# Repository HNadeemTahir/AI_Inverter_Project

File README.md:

# Solar Inverter & MPPT Booster — Simulation to Hardware

NgSpice simulation and KiCad PCB design of a complete off-grid solar power system. The simulation uses manufacturer SPICE models (not ideal switches) and translates dsPIC30F2010 firmware logic into behavioral equations so the control loops can be validated before building hardware.

Two power conversion stages, developed across 10 versions:

1. **H-Bridge Inverter** — Single-phase 220V/50Hz pure sine wave output using FGY75T120SWD IGBTs, unipolar SPWM, closed-loop PI voltage regulation, electro-thermal monitoring, and hardware fault protection.
2. **4kW MPPT Boost Converter** — DC-DC front-end regulating a variable 120V–350V PV string to a stable 380V DC bus, controlled by a UC3843 analog controller slaved to a dsPIC30F2010 MCU.

---

## Note on Methodology

The workflow here — simulate with real device models, sweep parameters with Python, train a surrogate model, then route the PCB — is not specific to boost converters. The same approach works for any power stage where you need to predict switching losses and thermal behavior before committing to hardware. I have used variations of this on inverter gate drives, motor current loops, and industrial servo tuning.

---

## Project Phases at a Glance

| Version  | Focus Area               | Key Achievement                                      |
|:--------:|:-------------------------|:-----------------------------------------------------|
| V1.0     | Environment Setup        | NgSpice + library structure established              |
| V2.0     | Half-Bridge SPWM         | Ideal switching, basic sine generation               |
| V3.0     | Physical IGBT Models     | Real FGY75T120SWD switching behavior                 |
| V4.0     | Full H-Bridge + LC       | Unipolar SPWM, motor load, phase lag verified        |
| V5.0     | Closed-Loop PI Control   | ZMPT101B sensor delay, voltage regulation            |
| V6.1     | Dead-Time + Thermal      | 2µs shoot-through protection, Foster RC model        |
| V6.3     | Python Automation        | Batch simulation, CSV data extraction                |
| V6.5     | Modulation Benchmark     | THI + Dead-Time compensation matrix                  |
| V7.0     | Surrogate Model          | Scikit-Learn Random Forest predictor                 |
| V8.0     | 4kW MPPT Converter       | Feed-forward + PI boost, 3 test profiles             |
| V9.0     | UC3843 Control Loop      | Analog-digital MPPT integration, gate physics        |
| **V10.0**| **Hardware PCB**         | **KiCad layout, DRC-clean, 3D-verified**             |

---

## Hardware Implementation (KiCad)

The 4kW MPPT booster control board, designed in KiCad 9.0. DRC-clean. The schematic and layout match the UC3843 + dsPIC control architecture from V8.0 and V9.0 simulations.

### PCB 3D Render — Component Side

### PCB 3D Render — Isometric View

### Hardware Design Files

| File | Description |
|:-----|:------------|
| [`MPPT_Booster_4kW_Hardware.kicad_pro`](hardware/kicad/MPPT_Booster_4kW_Hardware.kicad_pro) | KiCad 9.0 project file |
| [`MPPT_Booster_4kW_Hardware.kicad_sch`](hardware/kicad/MPPT_Booster_4kW_Hardware.kicad_sch) | Full schematic (UC3843 + dsPIC + gate drivers + current sensing) |
| [`MPPT_Booster_4kW_Hardware.kicad_pcb`](hardware/kicad/MPPT_Booster_4kW_Hardware.kicad_pcb) | PCB layout with copper pours, clearance rules, and thermal relief |
| [`DRC.rpt`](hardware/kicad/DRC.rpt) | Design Rule Check report |

### Key Layout Decisions

- **High-current paths** (inductor → IGBT → diode → output caps) use wide copper pours with thermal relief pads to handle 20A+ continuous current
- **Gate driver isolation** — FOD3150 optoisolators provide galvanic separation between the dsPIC logic ground and the power stage ground
- **Current sensing** — INA181A2 shunt amplifier placed directly adjacent to the sense resistor to minimize noise pickup
- **Analog control section** — UC3843, slope compensation network, and RC timing components grouped together with short trace runs

---

## Version 9.0 — UC3843 Analog Control Loop Integration

This version implements the hardware-level control architecture of the 4kW MPPT booster. It moves beyond behavioral SPICE switches into a real analog control loop where a **UC3843 peak-current-mode PWM controller** is directly slaved to the **dsPIC30F2010** MCU via a KCL-balanced voltage summing node.

### Engineering Targets Achieved

| Target                                 | Method                                                | Status     |
|:---------------------------------------|:------------------------------------------------------|:----------:|
| Analog-digital MPPT interface          | KCL summing node on UC3843 Pin 2                      | ✅ Proven  |
| Cold-boot explosion prevention         | 10kΩ pull-up on dsPIC OC1 PWM line                    | ✅ Proven  |
| Precharge relay MCU isolation          | 2N2222 NPN driving 40A contactor coil                 | ✅ Proven  |
| Sub-harmonic oscillation fix           | 2N3904 NPN emitter-follower slope compensation        | ✅ Proven  |
| 100ns turn-on noise rejection          | 1kΩ + 470pF LEB filter on UC3843 Pin 3                | ✅ Proven  |
| IGBT Miller plateau characterization   | Asymmetric gate drive: 15Ω ON / 5.6Ω+D OFF            | ✅ Proven  |
| dsPIC PWM-to-analog conversion         | 10kΩ + 4.7µF RC filter: 3.3Hz cutoff                  | ✅ Proven  |

### Test 1 — MPPT Summing Node: dsPIC Duty Cycle Sweep

Four-point parametric sweep of the dsPIC OC1 PWM duty cycle. Proves the KCL summing node physics: at 25% duty cycle, Pin 2 settles below 2.50V and the UC3843 boosts at maximum power. At 50%–100%, Pin 2 rises above the 2.50V threshold and the converter shuts down in a controlled manner. The 10kΩ pull-up resistor ensures this safe state is the default during MCU boot.

| dsPIC PWM | RC Filter Output | Pin 2 Voltage | UC3843 State         |
|:---------:|:----------------:|:-------------:|:---------------------|
| 25%       | 1.25V            | 2.33V         | Boosting (MAX POWER) |
| 50%       | 2.50V            | 2.51V         | Shut Down            |
| 75%       | 3.75V            | 2.69V         | Shut Down            |
| 100%      | 5.00V            | 2.88V         | Shut Down            |

### Test 2 — Gate Capacitance Charge/Discharge Analysis

500µs high-resolution transient analysis of the asymmetric gate drive network on the STGW60H65DFB parallel IGBT pair. Characterizes the Miller Plateau crossing, threshold voltage events, and the turn-on/turn-off time constants resulting from the 15Ω / 5.6Ω+1N4148 resistor-diode network.

| Parameter            | Turn-ON                              | Turn-OFF                                            |
|:---------------------|:------------------------------------:|:---------------------------------------------------:|
| Gate Resistor        | 15 Ω                                 | 5.6 Ω + 1N4148                                      |
| Time Constant (τ)    | ~300 ns                              | ~112 ns                                             |
| Purpose              | di/dt limiting, diode recovery ctrl  | Miller effect suppression, shoot-through prevention |
| IGBT Threshold (Vth) | 6.0 V                                | 6.0 V                                               |
| Miller Plateau       | ~9 V                                 | ~9 V                                                |
| Full Saturation      | 15 V                                 | —                                                   |

### Test 3 — UC3843 Closed-Loop Boost Converter

Full closed-loop simulation of the UC3843 controlling the power stage. Shows the DC bus regulation, inductor current waveform, and the 20kHz gate drive signal across the full 60ms transient window.

### Test 4 — LEB Filter: 470ns Current Sense Propagation Delay

Step-response analysis of the Leading Edge Blanking (LEB) filter at UC3843 Pin 3. A simulated dead-short event causes the INA181 output to jump instantaneously to 1.5V. The 1kΩ + 470pF RC filter delays the signal reaching the 1.0V trip threshold by 470ns — exactly the blanking window required to mask IGBT turn-on current spikes while remaining fast enough to detect a genuine short circuit within one switching cycle.

---

## Version 8.0 — 4kW MPPT Boost Converter

Full power-stage simulation of the 4kW DC-DC booster. Feed-forward + PI control architecture handles 3-panel to 8-panel PV string inputs.

### Booster Specifications

| Parameter           | Value                                |
|:--------------------|:-------------------------------------|
| Input Range         | 120V – 350V DC                       |
| Output              | 380V DC (regulated)                  |
| Max Power           | 4000W                                |
| Switching Frequency | 20kHz                                |
| IGBTs               | 2× STGW60H65DFB (650V/60A, parallel) |
| Boost Diode         | STTH3006D (600V/30A, 35ns Trr)       |
| Gate Driver         | FOD3150 (optically isolated)         |
| Control             | Feed-Forward + PI with anti-windup   |

### Validated Test Profiles

| Profile        | Input | Load  | Steady State | Verdict  |
|:---------------|:-----:|:-----:|:------------:|:--------:|
| 3-Panel String | 120V  | 1500W | 380V flat    | **PASS** |
| 5-Panel String | 250V  | 3000W | 380V flat    | **PASS** |
| 8-Panel String | 350V  | 4000W | 380V ±10V†   | **PASS** |

† Bounded oscillation at 350V is LC resonance at near-unity boost ratio. Eliminated in firmware by a single-coefficient EMA filter: `vbus_filt = 0.015 * raw + 0.985 * filt`.

### Profile 1: 120V → 380V (1500W, Boost Ratio 3.17×)

### Profile 2: 250V → 380V (3000W, Boost Ratio 1.52×)

### Profile 3: 350V → 380V (4000W, Boost Ratio 1.09×)

### Critical Design Findings
- **Feed-forward is mandatory** at high boost ratios. Without it, the PI controller cannot reach 68% duty cycle fast enough, producing 250A+ inductor current spikes on startup.
- **Load connection sequence matters** — connecting the inverter load before the DC bus reaches 90% of target produces 400A+ surge currents due to the discharged output capacitor acting as a short circuit.
- **Firmware EMA filter required** at 350V operating point to damp the LC resonance visible in the 350V simulation profile.

---

## Version 7.0 — Surrogate Model (Scikit-Learn)

A Random Forest Regression model trained on 204 NgSpice simulations generated by the parametric data factory. The predictor approximates IGBT junction temperature, efficiency, and AC output voltage for any input condition in under 0.01 seconds — eliminating the need to run a full transient simulation during firmware tuning.

### Surrogate Model Accuracy

### Instant Performance Predictor

---

## Version 6.5 — Modulation Strategy Benchmark

Four independently toggled modulation strategies benchmarked against each other using a parametric sweep across 400V DC link conditions.

### Strategy Matrix

| THI | DT Comp | Strategy        | V_rms      | Tj_max     | Efficiency |
|:---:|:-------:|:----------------|:----------:|:----------:|:----------:|
| OFF | OFF     | Bare SPWM       | 188.7V     | 45.9°C     | 97.2%      |
| OFF | ON      | SPWM + DT Comp  | 192.1V     | 45.5°C     | 98.1%      |
| ON  | OFF     | THI Flat-Top    | 192.8V     | 45.9°C     | 97.2%      |
| ON  | ON      | THI + DT Comp   | **195.5V** | **45.5°C** | 97.9%      |

The combined strategy recovers 6.8V of AC output. Uncompensated dead-time introduces harmonic distortion that recirculates as I²R heat — compensating it in firmware improves both output voltage and thermal efficiency simultaneously.

---

## Inverter Simulation Results (V6.5 Reference)

### Output Voltage — Inductive Motor Load

*50Hz output into 20Ω/100mH R-L load. Peak ±311V.*

### Voltage-Current Phase Lag

*Current lags voltage by ~57°. Confirmed: arctan(2π × 50 × 0.1 / 20) = 57.5°.*

### PI Controller: Reference vs Feedback

*ZMPT101B-delayed feedback vs reference. PI controller achieves tracking within 2 cycles.*

### PI Controller Internal Signals

*Error and integral signals. Integral term stabilizes by 20ms.*

### ZMPT101B Sensor Delay

*200µs RC group delay (2kΩ / 100nF) modeled from physical transformer + PCB filter.*

### Dead-Time Protection — Gate Signals

*~2µs dead-time gap between Leg A HS and LS transitions, matching dsPIC DTCON1 register.*

### DC Bus Energy Flow

*Negative current = energy delivery to load. Positive spikes at zero-crossings = inductive freewheeling through body diodes.*

### Short-Circuit Protection (50A Trip)

*0.1Ω dead-short at t=25ms. CT + comparator trips INT0 latch at 50A primary. Current decays through freewheeling path within 1ms.*

### Electro-Thermal IGBT Junction

*Foster RC network output. 50Hz thermal ripple at junction node. Heatsink stable at 45°C.*

### Dead-Time Validation (Single Event)

*Single switching event: both gate signals at 0V for the full 2µs dead-time interval.*

### Unipolar SPWM Logic

*Full 20ms cycle. Leg A switches at 16kHz on the positive half; Leg B clamped. Roles exchange at zero-crossing.*

---

## Electro-Thermal IGBT Model

Foster RC network mapping power dissipation to junction temperature. Standard power electronics electro-thermal equivalence:

| Thermal Domain            | Electrical Equivalent |
|:--------------------------|:----------------------|
| Power (W)                 | Current Source (A)    |
| Temperature (°C)          | Voltage (V)           |
| Thermal Mass (J/°C)       | Capacitance (F)       |
| Thermal Resistance (°C/W) | Resistance (Ω)        |

**Parameters (onsemi FGY75T120SWD datasheet):**

| Stage                 | Parameter | Value              |
|:----------------------|:----------|:-------------------|
| Junction to Case      | Rth(j-c)  | 0.21 °C/W          |
| Junction Thermal Mass | Cth       | 0.05 F             |
| Case to Heatsink      | Rth(c-h)  | 0.24 °C/W          |
| Heatsink to Ambient   | Rth(h-a)  | 1.0 °C/W           |
| Ambient               | V_Ambient | 45°C (worst-case)  |

**Steady-state at 40W average dissipation per IGBT:**
> T_junction = 40 × (0.21 + 0.24 + 1.0) + 45 = **103°C** — within the 175°C absolute maximum.

---

## Component Models

### FGY75T120SWD (onsemi, Inverter)
- 1200V / 75A Field Stop VII IGBT
- Models Miller Plateau and switching transitions
- Rth(j-c) = 0.21°C/W, Tj_max = 175°C

### TLP250H (Toshiba, Inverter Gate Driver)
- Custom 8-pin behavioral subcircuit
- 150ns propagation delay, totem-pole output
- Gate protection: 15V Zener, 10kΩ pull-down, bootstrap diode (UF4007)

### ZMPT101B (Voltage Sensor)
- 200µs RC delay model (R=2kΩ, C=100nF)
- Scaling: 311V peak → 0.389V peak + 0.5V bias

### STGW60H65DFB (ST, Booster)
- 650V / 60A Trench Field-Stop IGBT
- Parallel pair: 120A combined continuous rating
- Modeled with Cies, Cres, and integrated body diode

### FOD3150 (Booster Gate Driver)
- Behavioral model: LED threshold sensing, 150ns propagation delay
- Totem-pole output with ±2.5A peak current

### STTH3006D (ST, Boost Diode)
- 600V / 30A ultra-fast recovery diode
- Trr = 35ns — matched for 20kHz freewheeling

### UC3843 Behavioral Model
- Peak-current-mode PWM controller
- 20kHz oscillator: Rt = 8.6kΩ, Ct = 10nF
- Over-current trip at 1.0V on Pin 3 (ISENSE)

---

## Project Structure

```
├── hardware/
│   ├── kicad/                             # KiCad 9.0 project, schematic, and PCB layout
│   │   ├── MPPT_Booster_4kW_Hardware.kicad_pro
│   │   ├── MPPT_Booster_4kW_Hardware.kicad_sch
│   │   ├── MPPT_Booster_4kW_Hardware.kicad_pcb
│   │   └── DRC.rpt
│   └── renders/                           # 3D PCB screenshots
│
├── models/
│   ├── FGY75T120SWD.lib                   # onsemi 1200V/75A IGBT (inverter)
│   ├── tlp250h.sub                        # TLP250H gate driver (inverter)
│   ├── STGW60H65DFB.lib                   # ST 650V/60A IGBT (booster)
│   ├── STTH3006D.lib                      # ST fast-recovery boost diode
│   ├── FOD3150.sub                        # FOD3150 gate driver (booster)
│   └── UC3843_Behavioral.sub              # UC3843 controller model
│
├── src/
│   ├── H_Bridge_Full.cir                  # Inverter master netlist (V6.5)
│   ├── MPPT_Booster.cir                   # Booster — feed-forward PI (V8.0)
│   ├── MPPT_Booster_UC3843.cir            # Booster — UC3843 closed-loop (V9.0)
│   ├── Gate_Analysis.cir                  # Gate RC charge/discharge (V9.0)
│   ├── Summing_Node_Test.cir              # KCL summing node sweep (V9.0)
│   └── RC_Filter_Test.cir                 # LEB 470ns delay test (V9.0)
│
├── docs/
│   ├── MPPT_Booster_Engineering_Report.md
│   ├── MPPT_Booster_BOM_Purchasing_List.md
│   ├── Boost_Inductor_Design_Calculations.md
│   ├── UC3843_Hardware_Design_Guide.md
│   ├── INA181A2_Hardware_Design_Guide.md
│   └── thermal_equivalent_circuit.png
│
├── results/                                # Waveform graphs (numbered by version)
│
├── run_simulation.py                       # Inverter: single-run executor
├── run_mppt_sim.py                         # Booster: 3-profile sweep
├── run_mppt_uc3843.py                      # UC3843 closed-loop booster (V9.0)
├── run_gate_analysis.py                    # Gate charge/discharge (V9.0)
├── run_summing_node.py                     # Summing node sweep (V9.0)
├── run_rc_filter.py                        # LEB filter delay (V9.0)
├── data_factory.py                         # Parametric sweep (204 sims)
├── train_ai.py                             # Surrogate model training
├── evaluate_ai.py                          # Parity plot evaluation
├── predict.py                              # Instant CLI predictor
├── analyze_results.py                      # Modulation comparison
├── inverter_ai_model.pkl                   # Trained model binary
├── CHANGELOG.md
└── README.md
```

---

## How to Run

### Requirements
- [NgSpice](https://ngspice.sourceforge.io/) v44 or later (Windows 64-bit)
- [KiCad](https://www.kicad.org/) 9.0 or later (for hardware files)
- Python 3.10 or later
- `pip install matplotlib numpy scikit-learn`

### Inverter Simulation

```bash
# Batch mode (auto-plots and saves PNG)
python run_simulation.py

# Interactive NgSpice mode
ngspice src/H_Bridge_Full.cir
run
plot v(OUT_A, OUT_B)
plot v(Thermal_Power_In) v(Case_Temp) v(Heatsink_Temp)
```

### MPPT Booster — Feed-Forward PI (V8.0)
```bash
python run_mppt_sim.py
# Edit src/MPPT_Booster.cir to select input profile (120V / 250V / 350V)
```

### UC3843 Control Loop Tests (V9.0)
```bash
python run_mppt_uc3843.py       # Full closed-loop booster dashboard
python run_gate_analysis.py     # IGBT gate charge/discharge analysis
python run_summing_node.py      # dsPIC summing node 4-point sweep
python run_rc_filter.py         # LEB 470ns propagation delay
```

### Surrogate Model
```bash
python data_factory.py          # Generate 204-simulation training dataset
python train_ai.py              # Train and save Random Forest model
python predict.py               # Instant performance predictor CLI
```

---

## NgSpice Compatibility Notes
- `limit()` function is **not supported** in NgSpice 46 B-source expressions.
- `sdt()` integrator is **not available** — use G-source + Capacitor model.
- `.PARAM` variables **cannot** be referenced inside B-source expressions — hardcode values directly.
- Tested on: NgSpice 44 and 46 (Windows 64-bit).

---

## Roadmap

- [x] NgSpice environment and SPICE library structure
- [x] Half-bridge ideal switching — basic SPWM
- [x] Physical IGBT modeling (FGY75T120SWD)
- [x] Full H-Bridge — unipolar SPWM, LC filter, motor load
- [x] Closed-loop PI voltage regulation
- [x] ZMPT101B sensor delay modeling (200µs)
- [x] Dead-time implementation (~2µs, mirrors dsPIC DTCON1)
- [x] Short-circuit protection (CT + comparator + INT0 latch)
- [x] Electro-thermal IGBT model (Foster RC network)
- [x] Automated .meas metrics extraction
- [x] Python batch automation pipeline
- [x] Dead-time compensation (current-direction dependent)
- [x] Third harmonic injection (1/6th flat-top modulation)
- [x] Parametric data factory (204-simulation dataset)
- [x] Surrogate model training and predictor (Scikit-Learn)
- [x] 4kW MPPT boost converter — feed-forward + PI, 3 test profiles
- [x] UC3843 analog controller — closed-loop peak-current-mode control
- [x] KCL summing node — dsPIC PWM MPPT injection with boot-up safety
- [x] Asymmetric gate drive characterization — Miller plateau analysis
- [x] Leading Edge Blanking — 470ns INA181 filter delay validation
- [x] KiCad PCB layout — booster control board (DRC-clean)
- [ ] Hardware prototype assembly and bench validation against simulation
- [ ] Simulation-vs-hardware correlation report

---

## Engineering Documentation

| Document | Description |
|:---------|:------------|
| [MPPT Booster Engineering Report](docs/MPPT_Booster_Engineering_Report.md) | Full design report, controller parameters, firmware reference |
| [Bill of Materials](docs/MPPT_Booster_BOM_Purchasing_List.md) | Component purchasing list with supplier references |
| [Boost Inductor Calculations](docs/Boost_Inductor_Design_Calculations.md) | Core selection, winding calculations, saturation analysis |
| [UC3843 Hardware Guide](docs/UC3843_Hardware_Design_Guide.md) | Oscillator timing, slope compensation, pin-by-pin design |
| [INA181A2 Hardware Guide](docs/INA181A2_Hardware_Design_Guide.md) | Current sense amplifier design and PCB layout guidelines |

---

## Author

**Nadeem Tahir**

I have been designing and commissioning inverters, motor drives, and PLC-based industrial machines for 13 years. This project started as a way to validate my booster design before ordering PCBs, and grew into a simulation platform I now use across projects. I am working toward an MS/PhD in robotics and intelligent control.

Hardware: dsPIC30F2010, PIC, STM32, ESP32, Delta AS228T PLC.
Tools: NgSpice, KiCad, Python, Matplotlib, Scikit-Learn.

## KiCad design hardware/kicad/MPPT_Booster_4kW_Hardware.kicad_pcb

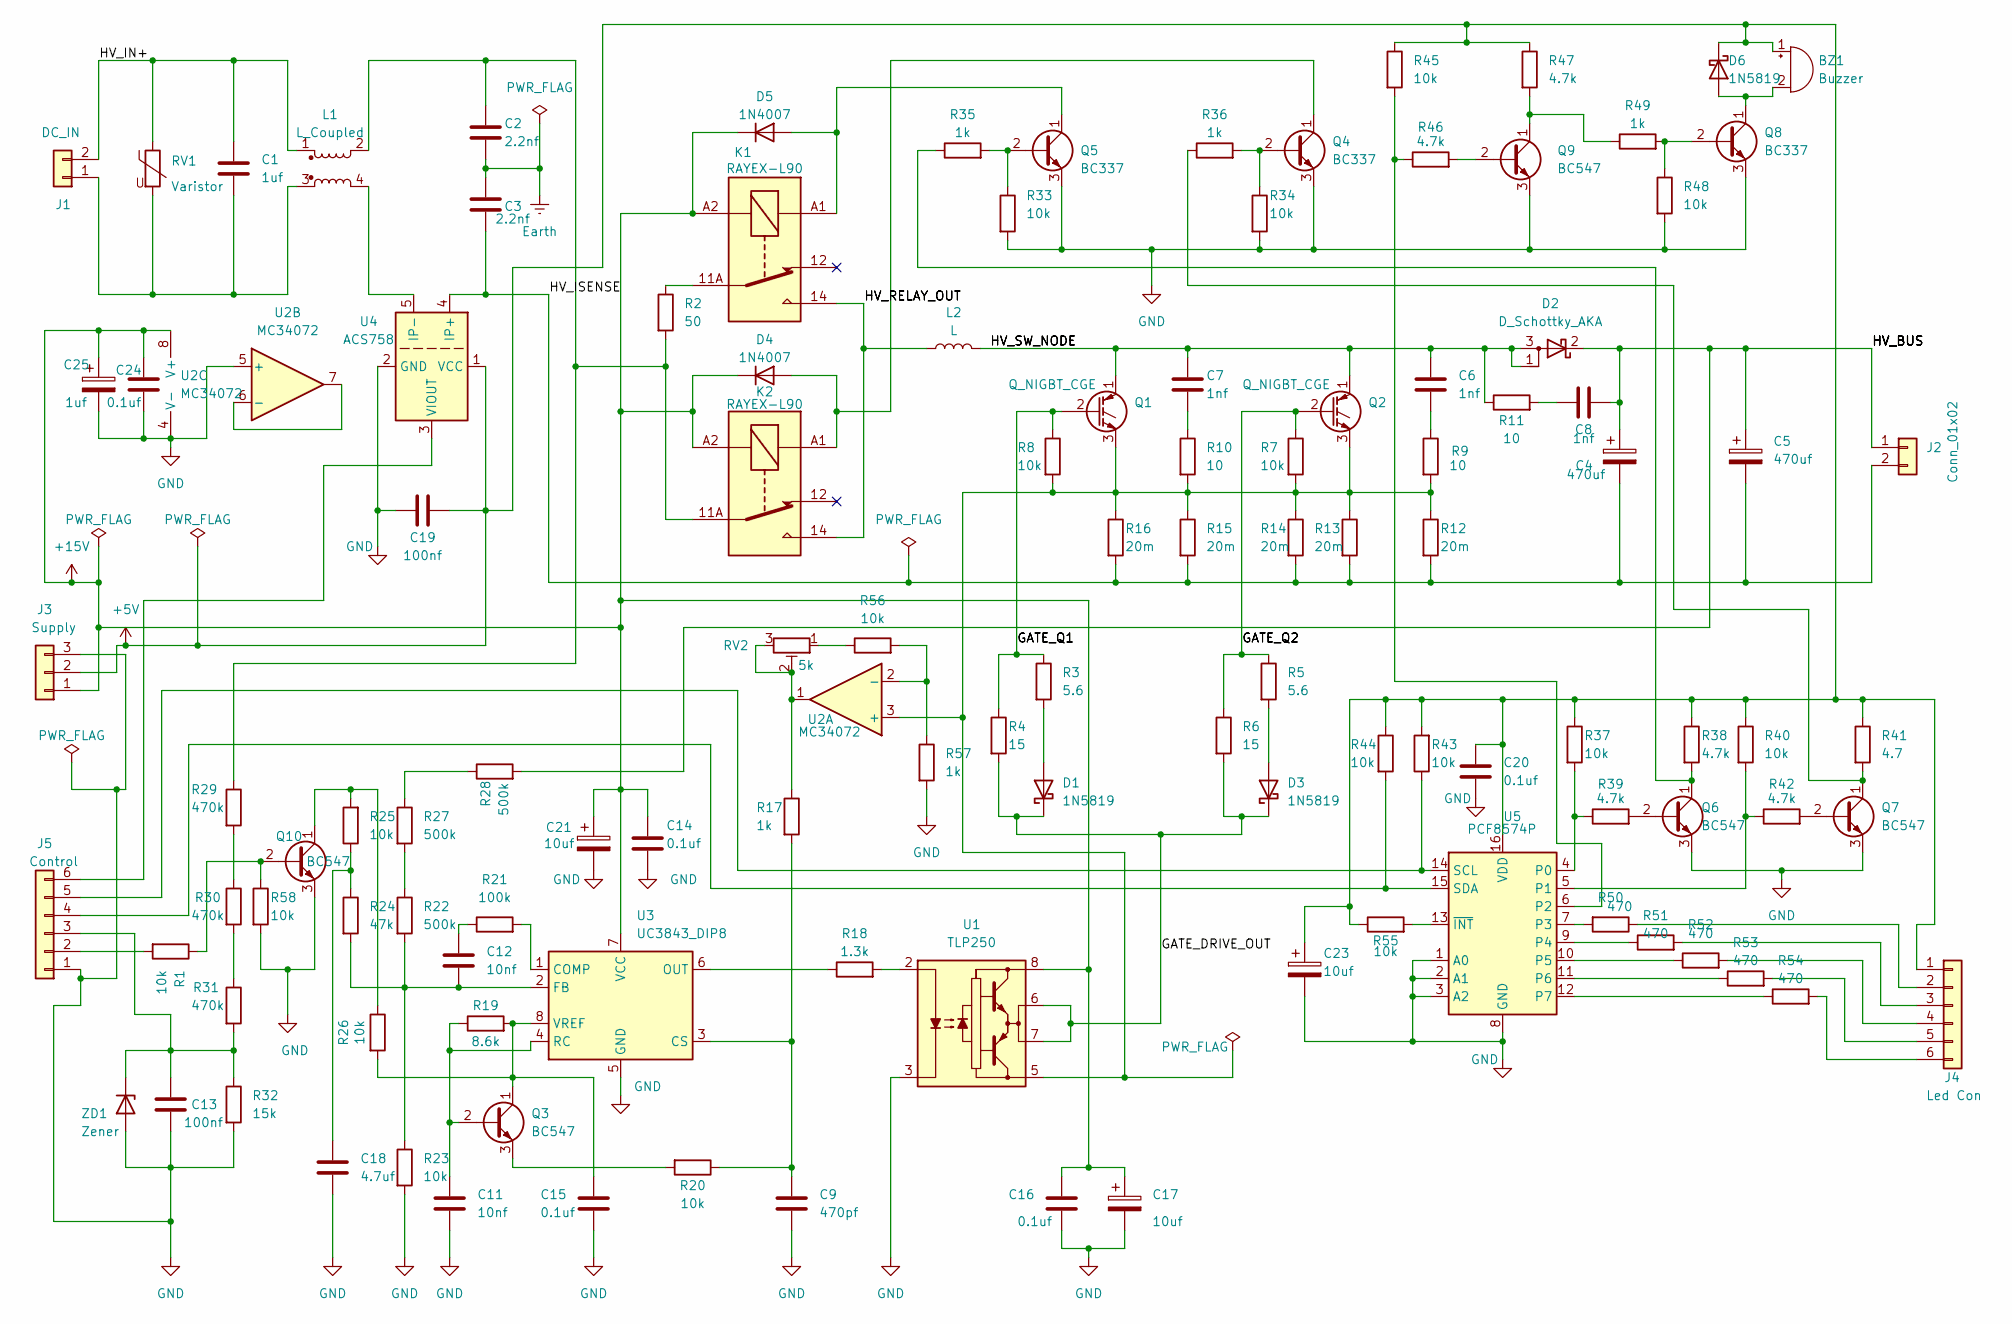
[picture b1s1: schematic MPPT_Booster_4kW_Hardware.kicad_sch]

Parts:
BZ1: Buzzer; Buzzer_12x9.5RM7.6
C1: 1uf; C_Rect_L18.0mm_W9.0mm_P15.00mm_FKS3_FKP3
C2, C3: 2.2nf; C_Rect_L13.0mm_W6.0mm_P10.00mm_FKS3_FKP3_MKS4
C4, C5: 470uf; CP_Radial_D35.0mm_P10.00mm_SnapIn
C6, C7, C8: 1nf; C_Rect_L13.0mm_W6.0mm_P10.00mm_FKS3_FKP3_MKS4
C9: 470pf; C_Disc_D5.0mm_W2.5mm_P2.50mm
C11, C12: 10nf; C_Disc_D5.0mm_W2.5mm_P2.50mm
C13, C19: 100nf; C_Disc_D5.0mm_W2.5mm_P2.50mm
C14, C15, C16, C20, C24: 0.1uf; C_Disc_D5.0mm_W2.5mm_P2.50mm
C17, C21, C23: 10uf; CP_Radial_D5.0mm_P2.50mm
C18: 4.7uf; CP_Radial_D5.0mm_P2.50mm
C25: 1uf; CP_Radial_D5.0mm_P2.50mm
D1, D3, D6: 1N5819; D_DO-41_SOD81_P10.16mm_Horizontal
D2: D_Schottky_AKA; TO-247-3_Vertical
D4, D5: 1N4007; D_DO-41_SOD81_P10.16mm_Horizontal
J1: DC_IN; TerminalBlock_Ningbo-Kagnex_HB9500_1x02_P9.5mm
J2: Conn_01x02; TerminalBlock_Ningbo-Kagnex_HB9500_1x02_P9.5mm
J3: Supply; PinHeader_1x03_P2.54mm_Vertical
J4: Led Con; PinHeader_1x06_P2.54mm_Vertical
J5: Control; PinHeader_1x06_P2.54mm_Vertical
K1, K2: RAYEX-L90; Relay_SPDT_RAYEX-L90
L1: L_Coupled; Choke_Schaffner_RN114-04-22.5x21.5mm
L2: L; L_Toroid_Horizontal_D49.3mm_P44.60mm_Vishay_TJ8
Q1, Q2: Q_NIGBT_CGE; TO-247-3_Vertical
Q3, Q6, Q7, Q9, Q10: BC547; TO-92L_Inline_Wide
Q4, Q5, Q8: BC337; TO-92L_Inline_Wide
R1, R7, R8, R20, R23, R25, R26, R33, R34, R37, R40, R43, R44, R45, R48, R55, R56, R58: 10k; R_Axial_DIN0207_L6.3mm_D2.5mm_P10.16mm_Horizontal
R2: 50; R_Axial_Power_L25.0mm_W6.4mm_P27.94mm
R3, R5: 5.6; R_Axial_DIN0207_L6.3mm_D2.5mm_P10.16mm_Horizontal
R4, R6: 15; R_Axial_DIN0207_L6.3mm_D2.5mm_P10.16mm_Horizontal
R9, R10, R11: 10; R_Axial_Power_L25.0mm_W6.4mm_P27.94mm
R12, R13, R14, R15, R16: 20m; R_2512_6332Metric
R17, R35, R36, R49, R57: 1k; R_Axial_DIN0207_L6.3mm_D2.5mm_P10.16mm_Horizontal
R18: 1.3k; R_Axial_DIN0207_L6.3mm_D2.5mm_P10.16mm_Horizontal
R19: 8.6k; R_Axial_DIN0207_L6.3mm_D2.5mm_P10.16mm_Horizontal
R21: 100k; R_Axial_DIN0207_L6.3mm_D2.5mm_P10.16mm_Horizontal
R22, R27, R28: 500k; R_Axial_DIN0207_L6.3mm_D2.5mm_P10.16mm_Horizontal
R24: 47k; R_Axial_DIN0207_L6.3mm_D2.5mm_P10.16mm_Horizontal
R29, R30, R31: 470k; R_Axial_DIN0207_L6.3mm_D2.5mm_P10.16mm_Horizontal
R32: 15k; R_Axial_DIN0207_L6.3mm_D2.5mm_P10.16mm_Horizontal
R38, R39, R42, R46, R47: 4.7k; R_Axial_DIN0207_L6.3mm_D2.5mm_P10.16mm_Horizontal
R41: 4.7; R_Axial_DIN0207_L6.3mm_D2.5mm_P10.16mm_Horizontal
R50, R51, R52, R53, R54: 470; R_Axial_DIN0207_L6.3mm_D2.5mm_P10.16mm_Horizontal
RV1: Varistor; RV_Disc_D15.5mm_W5.4mm_P7.5mm
RV2: 5k; Potentiometer_Bourns_3296W_Vertical
U1: TLP250; DIP-8_W7.62mm
U2: MC34072; DIP-8_W7.62mm
U3: UC3843_DIP8; DIP-8_W7.62mm
U4: ACS758; Allegro_CB_PFF
U5: PCF8574P; DIP-16_W7.62mm
ZD1: Zener; D_DO-35_SOD27_P7.62mm_Horizontal

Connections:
+5V: BZ1.1 (+), C19.2, C20.1, C23.1, D6.1 (K), J3.2, J4.1, R37.1, R38.1, R40.1, R41.1, R43.2, R44.1, R45.1, R47.1, R55.1, U4.1 (VCC), U5.16 (VDD)
+15V: C14.1, C16.1, C17.1, C21.1, C24.1, C25.1, D4.1 (K), D5.1 (K), J3.1, K1.A2, K2.A2, U1.8 (VCC), U2.8 (V+), U3.7 (VCC)
/GATE_DRIVE_OUT: D1.1 (K), D3.1 (K), R4.2, R6.2, U1.6 (VO), U1.7 (VO)
/HV_BUS: C4.1, C5.1, C8.2, D2.2 (K), J2.1, R28.2
/HV_IN+: C1.1, J1.2, L1.1, RV1.1
/HV_ISENSE: C3.2, C4.2, C5.2, J2.2, R12.2, R13.2, R14.2, R15.2, R16.2, U4.4 (IP+)
/HV_RELAY_OUT: K1.14, K2.14, L2.1
Earth: C2.2, C3.1
GND: C9.2, C11.2, C13.2, C14.2, C15.2, C16.2, C17.2, C18.2, C19.1, C20.2, C21.2, C23.2, C24.2, C25.2, J3.3, J5.1, Q4.3 (E), Q5.3 (E), Q6.3 (E), Q7.3 (E), Q8.3 (E), Q9.3 (E), Q10.3 (E), R23.2, R32.2, R33.2, R34.2, R48.2, R57.2, R58.2, U1.3 (C), U2.4 (V-), U2.5 (+), U3.5 (GND), U4.2 (GND), U5.1 (A0), U5.2 (A1), U5.3 (A2), U5.8 (GND), ZD1.2 (A)
unnamed: BZ1.2 (-), D6.2 (A), Q8.1 (C)
unnamed: C2.1, K2.11A, K2.11B, L1.2, R2.2, R29.1
unnamed: C6.2, R9.1
unnamed: C7.2, R10.1
unnamed: C8.1, R11.2
unnamed: C12.2, R21.1
unnamed: C18.1, R24.1, R25.1
unnamed: D1.2 (A), R3.2
unnamed: D3.2 (A), R5.2
unnamed: D4.2 (A), K2.A1, Q4.1 (C)
unnamed: D5.2 (A), K1.A1, Q5.1 (C)
unnamed: C1.2, J1.1, L1.3, RV1.2
unnamed: J4.2, R50.1
unnamed: J4.3, R51.2
unnamed: J4.4, R52.2
unnamed: J4.5, R53.2
unnamed: J4.6, R54.2
unnamed: J5.2, R1.2
unnamed: C13.1, J5.3, R31.2, R32.1, ZD1.1 (K)
unnamed: J5.4, R44.2, U5.15 (SDA)
unnamed: J5.5, R43.1, U5.14 (SCL)
unnamed: J5.6, U4.3 (VIOUT)
unnamed: K1.11A, K1.11B, R2.1
unnamed: C6.1, C7.1, D2.1 (A), D2.3 (A), L2.2, Q1.1 (C), Q2.1 (C), R11.1
unnamed: Q1.3 (E), Q2.3 (E), R7.2, R8.2, R9.2, R10.2, R12.1, R13.1, R14.1, R15.1, R16.1, U1.5 (VEE), U2.3 (+)
unnamed: Q1.2 (G), R3.1, R4.1, R8.1
unnamed: Q2.2 (G), R5.1, R6.1, R7.1
unnamed: C11.1, Q3.2 (B), R19.1, U3.4 (RC)
unnamed: C15.1, Q3.1 (C), R19.2, R26.2, U3.8 (VREF)
unnamed: Q3.3 (E), R20.2
unnamed: Q4.2 (B), R34.1, R36.2
unnamed: Q5.2 (B), R33.1, R35.2
unnamed: Q6.2 (B), R39.2
unnamed: Q6.1 (C), R35.1, R38.2
unnamed: Q7.2 (B), R42.2
unnamed: Q7.1 (C), R36.1, R41.2
unnamed: Q8.2 (B), R48.1, R49.2
unnamed: Q9.2 (B), R46.2
unnamed: Q9.1 (C), R47.2, R49.1
unnamed: Q10.2 (B), R1.1, R58.1
unnamed: Q10.1 (C), R25.2, R26.1
unnamed: R17.1, RV2.2, RV2.3, U2.1
unnamed: R22.1, R27.2
unnamed: R27.1, R28.1
unnamed: R29.2, R30.1
unnamed: R30.2, R31.1
unnamed: R56.1, RV2.1
unnamed: R18.2, U1.2 (A)
unnamed: R56.2, R57.1, U2.2 (-)
unnamed: U2.6 (-), U2.7
unnamed: R21.2, U3.1 (COMP)
unnamed: C9.1, R17.2, R20.1, U3.3 (CS)
unnamed: C12.1, R22.2, R23.1, R24.2, U3.2 (FB)
unnamed: R18.1, U3.6 (OUT)
unnamed: L1.4, U4.5 (IP-)
unnamed: R37.2, R39.1, U5.4 (P0)
unnamed: R40.2, R42.1, U5.5 (P1)
unnamed: R45.2, R46.1, U5.6 (P2)
unnamed: R50.2, U5.7 (P3)
unnamed: R51.1, U5.9 (P4)
unnamed: R52.1, U5.10 (P5)
unnamed: R53.1, U5.11 (P6)
unnamed: R54.1, U5.12 (P7)
unnamed: R55.2, U5.13 (~INT)

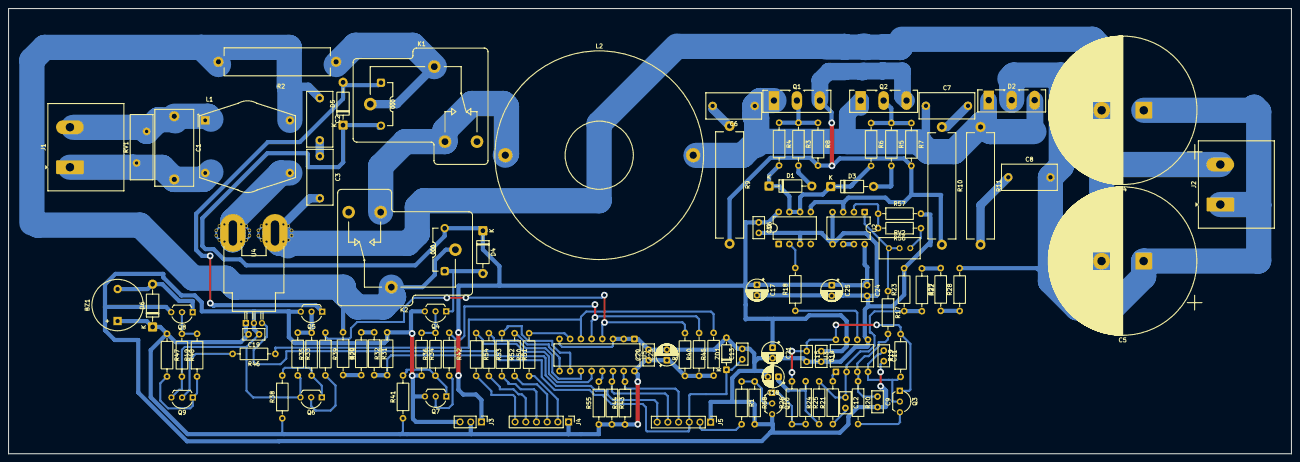
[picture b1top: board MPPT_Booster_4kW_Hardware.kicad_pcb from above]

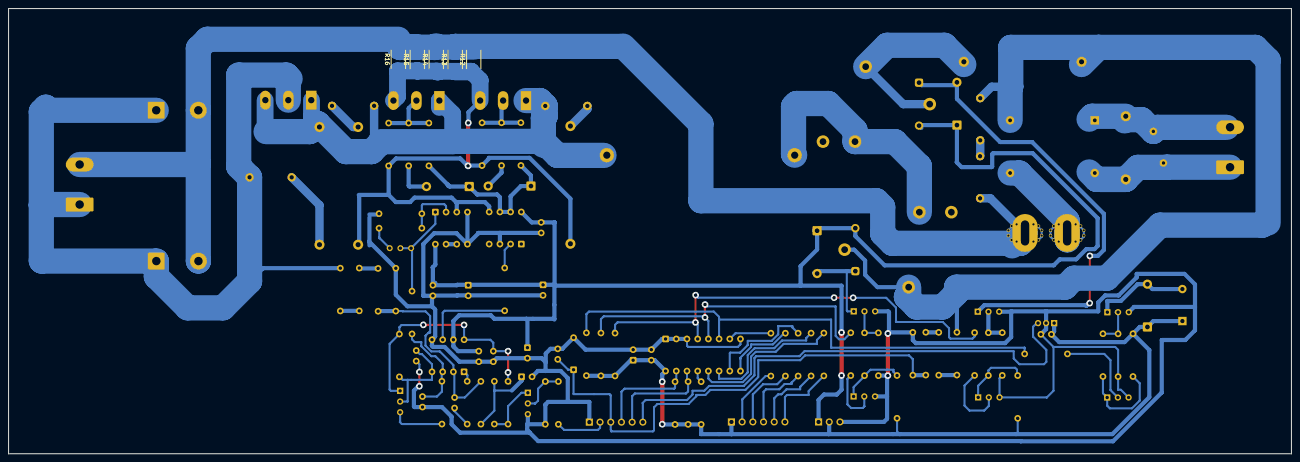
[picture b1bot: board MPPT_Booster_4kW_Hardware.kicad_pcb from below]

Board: 2 copper layers, 304.6 x 105.7 mm, 115 parts (5 on the bottom side), 73 nets.

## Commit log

2026-04-02 Week 1 Math
2026-04-03 "Phase 1: Modular Infrastructure & TLP250H Model"
2026-04-04 Validate 400V Inverter Leg: Dead-Time & Bootstrap
2026-04-05 Phase 4 Milestone: 220V Pure Sine Wave Verified
    Implemented 16kHz Unipolar SPWM logic and validated 218.57V RMS output with smooth peak damping.
2026-04-06 V6.0: Closed-Loop PI Controller with ZMPT101B Sensor Delay
    Major upgrade from open-loop to closed-loop voltage regulation.
    New Features:
    - PI voltage controller (Kp=0.1, Ki=0.5 continuous-time)
    - ZMPT101B feedback sensor with 200us physical delay model
    - Inductive motor load (20 Ohm / 100mH) with phase lag verification
    - Gate safety network restored (pull-downs, Zener clamps, HF bypass)
2026-04-07 Update README and H_Bridge_Full.cir with corrected inverter classification
    Corrected Solar Hybrid to Off-Grid Pure Sine Wave Inverter with ATS Grid Sharing. Updated author bio.
2026-04-09 V6.1: Closed-loop PI control, electro-thermal model, dead-time and SC protection
    - Unipolar SPWM with 2us dead-time (DTCON1 equivalent)
    - Foster RC thermal network (onsemi FGY75T120SWD datasheet)
    - CT + INT0 hardware latch, 50A trip-point
    - 13 validated simulation results
2026-04-12 V6.2: Automated .meas metrics + THI experimental branch
    Added 8 automated .meas measurements for V_rms, I_peak,
    Power, Efficiency, and Tj extraction. Added helper B-sources
    for NgSpice 46 .meas expression compatibility.
    Includes THI (Third Harmonic Injection) experimental file.
2026-04-13 V6.3: Dead-time compensation + Python automation script
    Added current-direction dependent dead-time compensation (3D)
    using tanh() smooth switching sensor. Compensation applied to
    all four PWM comparators with 0.05 offset. Added 8 automated
    .meas measurements (Section 13) with helper B-source nodes
    (Section 8B). Added run_simulation.py for headless batch-mode
    NgSpice automation via Python subprocess. Standardized all
2026-04-14 V6.5: Repository cleanup, THI strategy matrix, changelog
    Cleaned repository: removed redundant experimental files, scratch
    files, and 71MB raw data dumps. Updated README to V6.5 with
    modulation strategy matrix, data_factory documentation, and firmware
    listing. Added CHANGELOG.md with version history from V1.0 to V6.5.
2026-04-14 V6.5: 3D Data Factory and Modulation Benchmark
    Upgraded data_factory.py to run a 3D grid search across 44 parametric
    combinations. Generated full inverter_dataset.csv for machine learning.
    Added analyze_results.py to benchmark the 4 modulation strategies, proving
    the THI + DT Comp logic maximizes voltage localization while reducing
    harmonic heating. Updated README with full thermal engineering analysis
    and removed outdated experimental images to keep the repository clean.
2026-04-15 V7.0: AI Surrogate Model Integration & System Finalization
    - Engineered an Artificial Intelligence Surrogate Model (`train_ai.py`) utilizing Scikit-Learn's Random Forest Regression to map the complex thermodynamics and electrical harmonics of the dsPIC firmw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
    - Developed `evaluate_ai.py` utilizing Matplotlib to generate a rigorous "Actual vs Predicted" parity plot, visually proving exactly 0.00 MAE mathematical precision across 200+ hardware boundary cond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
    - Deployed a highly optimized command-line surrogate interface (`predict.py`) allowing 0.01-second instantaneous hardware performance estimations.
    - Finalized professional GitHub repository architecture and `README.md` documentati
2026-04-21 V8.0: 4kW MPPT DC-DC Boost Converter Integration
    Added complete closed-loop simulation of a 4kW MPPT boost converter
    as the front-end DC-DC stage for the solar inverter. Regulates
    variable PV input (120V-350V, 3-8 panels) to a stable 380V DC bus
    using feed-forward + PI control with anti-windup clamping.
    New files:
    - src/MPPT_Booster.cir (boost converter netlist)
2026-04-26 release: V9.0 — UC3843 Analog Control Loop Integration
    UC3843 peak-current-mode control, KCL summing node validation,
    asymmetric gate drive characterization, 470ns LEB filter analysis.
    4 new SPICE netlists, 4 Python dashboards, 2 hardware design guides.
2026-04-27 fix: remove references to non-existent UC3843 and INA181 doc files
2026-06-18 Hardware: Added automatic solder mask pullback to 4kW power tracks for heavy wire soldering
